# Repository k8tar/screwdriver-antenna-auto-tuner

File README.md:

# Screwdriver Antenna Auto Tuner

An ESP32-based automatic controller for motorized HF screwdriver antennas.

This repository contains the firmware, generated KiCad design files, enclosure
model, sourcing notes, build documentation, renders, and fabrication outputs for
an in-vehicle automatic antenna tuner with:

- ESP32 control logic
- OLED status display
- motor drive with current-based stall detection
- SWR measurement using an onboard directional coupler
- detachable radio and antenna harnesses
- Tarheel-style sensor support via the 4-wire antenna connector

## Current revision highlights

- single-mode auto-tuner firmware with TUNE, PARK, and jog controls
- power-stage revision to the Murata OKI-78SR fixed 3.3 V regulator
- external SWR jack removed from the PCB revision
- updated enclosure previews and board renders
- regenerated Gerber package in `fab/tuner_gerbers.zip`
- printable enclosure assets can be exported directly from OpenSCAD, with 3MF
	files generated for the current base and lid geometry

## Screenshots

Board render:

Assembled enclosure preview:

Service-open enclosure preview:

## Repository layout

- `firmware/` — PlatformIO firmware, simulation wiring, and firmware spec
- `hardware/` — assembly guide, BOM, sourcing, routing notes, enclosure model
- `hardware/kicad/` — generated KiCad schematic, PCB, netlist, DSN, footprints
- `renders/` — board and enclosure images plus schematic and PCB PDFs
- `fab/` — generated Gerbers and fabrication ZIP package
- `scripts/` — source-of-truth generators for schematic, PCB, BOM, and fab outputs

## Quick start

1. Read the hardware requirements and build notes in `hardware/ASSEMBLY.md`.
2. Review the firmware contract in `firmware/FIRMWARE_SPEC.md`.
3. Build firmware from `firmware/` with PlatformIO.
4. If you are fabricating the PCB, use `fab/tuner_gerbers.zip`.
5. If you are printing the enclosure, use the generated 3MF files in
	`hardware/enclosure/` or export fresh parts from `hardware/enclosure/enclosure.scad`.

## First-time builder checklist

1. Read `hardware/ASSEMBLY.md` start to finish before soldering anything.
2. Confirm you are building the **Murata OKI-78SR** power-stage revision, not the older adjustable U1 variant.
3. Order parts from `hardware/BOM.csv` and review substitutions in `hardware/SOURCING.md`.
4. Verify your enclosure connector choices against `hardware/RADIO_CONNECTOR.md` and `hardware/enclosure/README.md`.
5. Print or export the enclosure parts you want before final panel-harness lengths are cut.
6. Build and test the firmware in `firmware/` before final in-vehicle installation.
7. Power the assembled board from a current-limited bench supply first.
8. Program the ESP32 DevKit over USB and verify the OLED, buttons, PARK, and jog behavior before connecting the antenna.
9. Run `PARK` once after wiring a Tarheel-style sensor harness so the controller establishes home.

## Prerequisites

- Python 3 for the generator scripts
- PlatformIO for firmware builds
- KiCad CLI available through the configured Flatpak commands for schematic/PCB regeneration
- OpenSCAD for enclosure previews and print-file export

## Build and generation

Firmware build:

```bash
cd firmware
pio run
```

Firmware upload:

```bash
cd firmware
pio run -t upload
pio device monitor
```

Hardware regeneration from the repo root:

```bash
python3 scripts/gen_footprints.py
python3 scripts/gen_schematic.py
flatpak run --command=kicad-cli org.kicad.KiCad sch export netlist -o hardware/kicad/tuner.net hardware/kicad/tuner.kicad_sch
flatpak run --command=python3 org.kicad.KiCad scripts/gen_pcb.py
flatpak run --command=python3 org.kicad.KiCad scripts/export_dsn.py
python3 scripts/gen_bom.py
python3 scripts/gen_gerbers.py
```

Enclosure print export:

```bash
cd hardware/enclosure
openscad -D 'part="base"' -o base.stl enclosure.scad
openscad -D 'part="lid"' -o lid.stl enclosure.scad
openscad -D 'part="both"' -o enclosure_full.stl enclosure.scad
openscad -D 'part="base"' -o base.3mf enclosure.scad
openscad -D 'part="lid"' -o lid.3mf enclosure.scad
openscad -D 'part="both"' -o enclosure_full.3mf enclosure.scad
```

## Primary documentation

- `firmware/FIRMWARE_SPEC.md`
- `firmware/src/README.md`
- `hardware/ASSEMBLY.md`
- `hardware/SOURCING.md`
- `hardware/RADIO_CONNECTOR.md`
- `hardware/enclosure/README.md`

## Fabrication outputs

- PCB fabrication ZIP: `fab/tuner_gerbers.zip`
- Individual Gerbers/drill files: `fab/gerbers/`
- Enclosure print files: `hardware/enclosure/base.stl`, `hardware/enclosure/lid.stl`, `hardware/enclosure/enclosure_full.stl`, `hardware/enclosure/base.3mf`, `hardware/enclosure/lid.3mf`, `hardware/enclosure/enclosure_full.3mf`
- Board and enclosure previews: `renders/`

## Programming the ESP32

This design uses an ESP32 DevKit module as `U2`, so the easiest programming path
is through the DevKit's normal USB port.

Typical workflow:

1. Assemble the board and fit the ESP32 DevKit at `U2`.
2. Power the board from a current-limited 12 V bench supply for first bring-up.
3. Connect the ESP32 DevKit USB port to your computer.
4. From the `firmware/` directory, run:

```bash
pio run -t upload
pio device monitor
```

If you ever need direct serial flashing instead of the DevKit USB connector, use
the debug UART header `J8` with a 3.3 V USB-to-UART adapter.

Recommended `J8` signals:

- pin 1 = GND
- pin 2 = 3V3
- pin 3 = TX from ESP32
- pin 4 = RX to ESP32

For most builds, you do **not** need to power the ESP32 through `J8`; just share
ground and use the DevKit USB interface unless you have a special recovery case.

## Notes

- The generated KiCad files in `hardware/kicad/` are derived artifacts; the
	Python scripts in `scripts/` are the source of truth.
- For vehicle use, internal board wiring should be direct-soldered and strain
	relieved rather than using loose jumper leads.
- The pre-generated STL and 3MF files are convenience outputs for the current
	enclosure geometry; regenerate them from `hardware/enclosure/enclosure.scad` if
	you change any enclosure parameters. `enclosure_full.3mf` and
	`enclosure_full.stl` contain the base and lid together as one combined export.

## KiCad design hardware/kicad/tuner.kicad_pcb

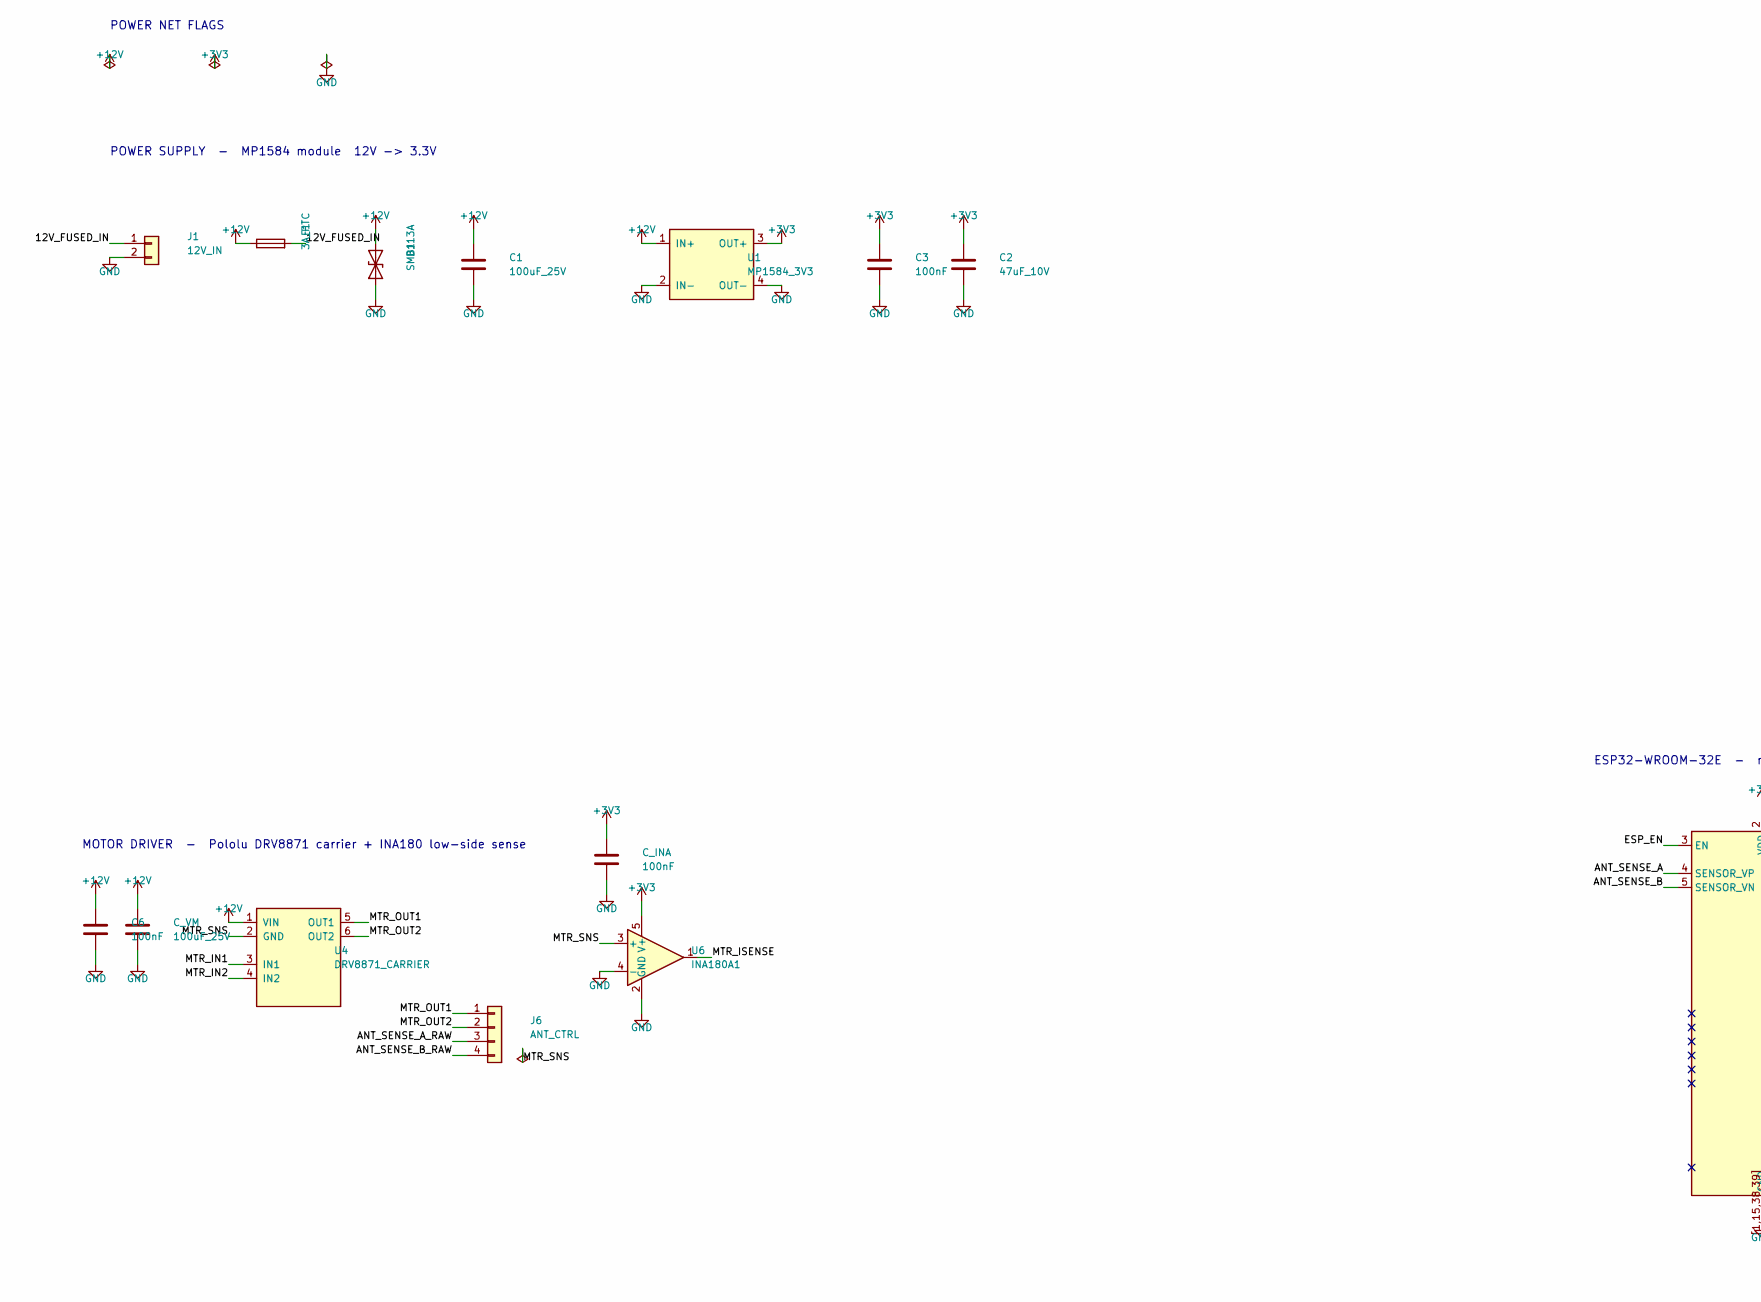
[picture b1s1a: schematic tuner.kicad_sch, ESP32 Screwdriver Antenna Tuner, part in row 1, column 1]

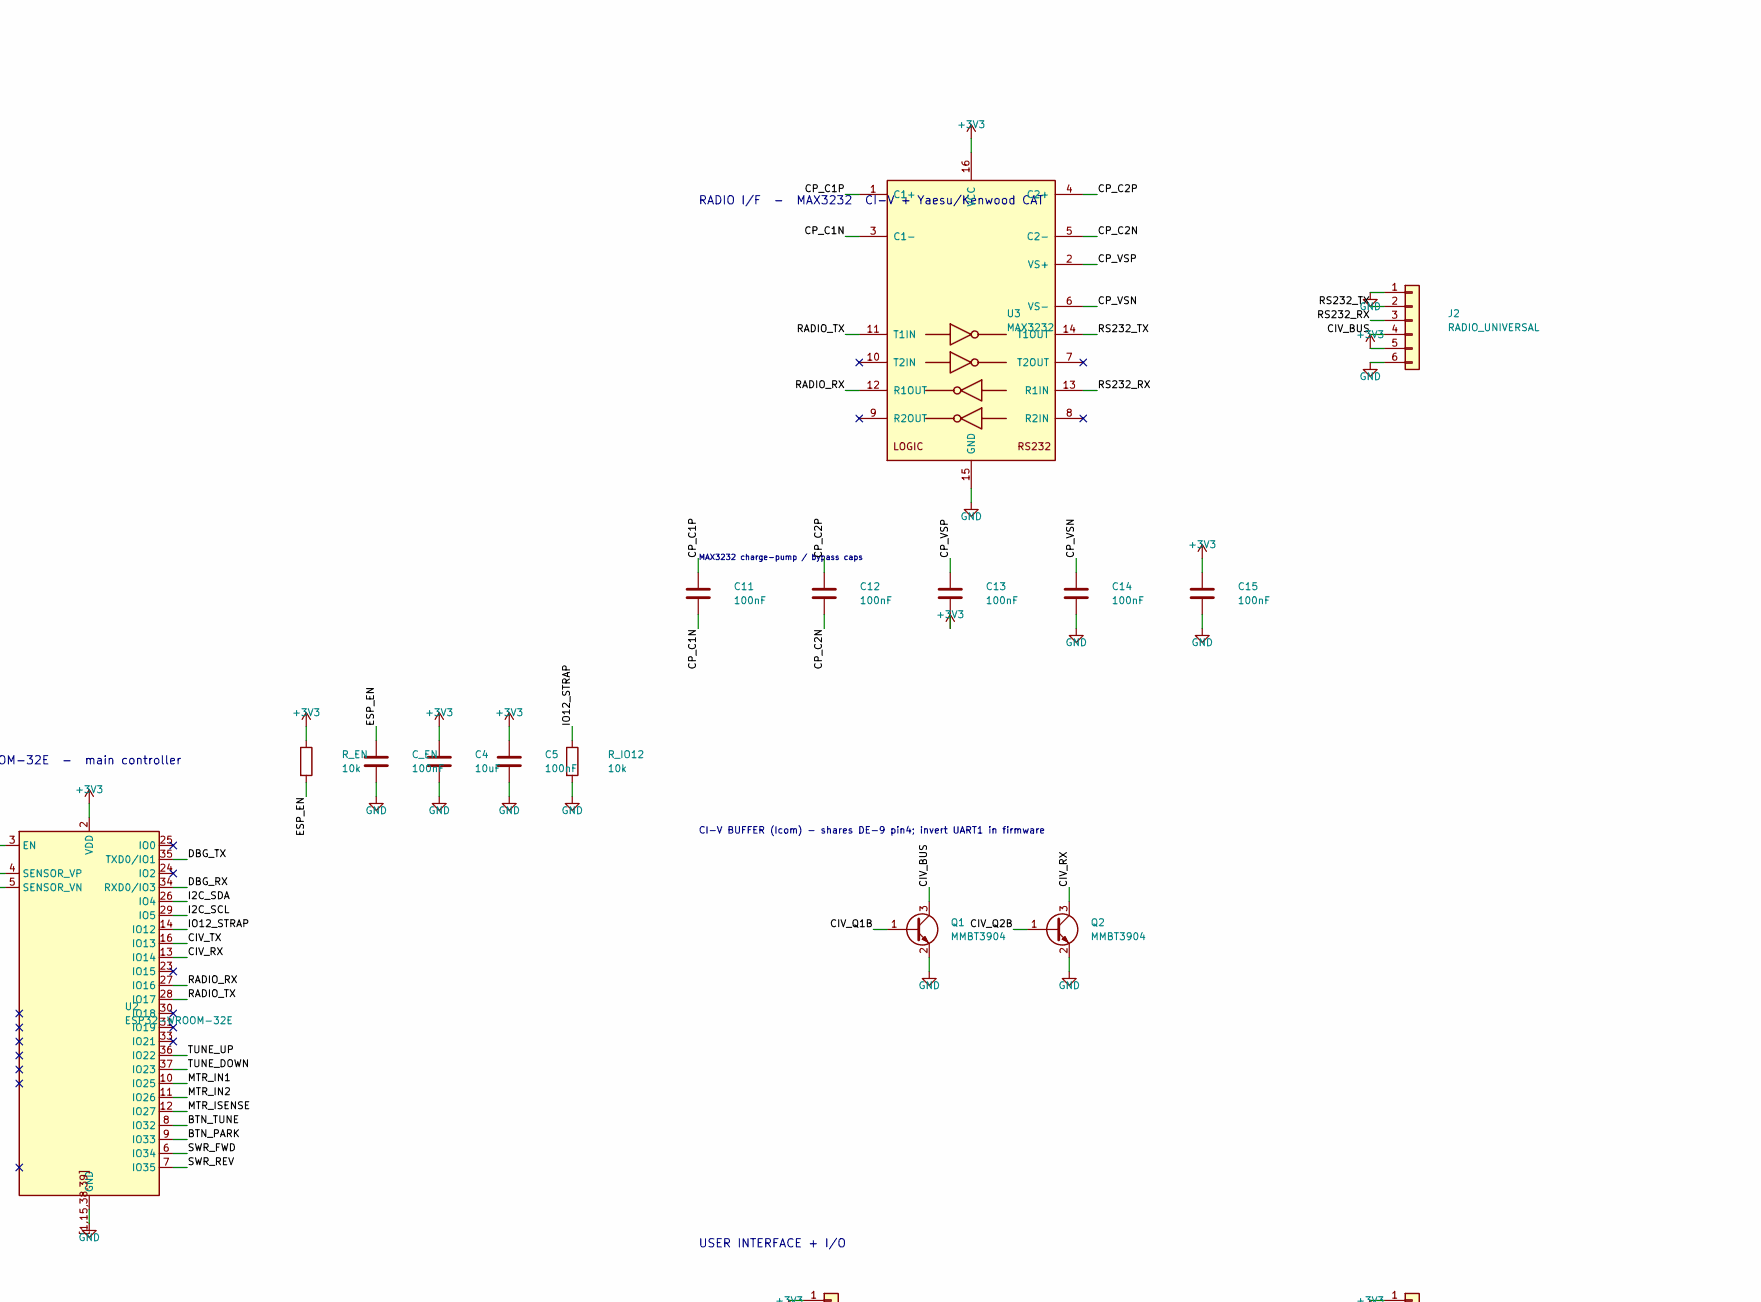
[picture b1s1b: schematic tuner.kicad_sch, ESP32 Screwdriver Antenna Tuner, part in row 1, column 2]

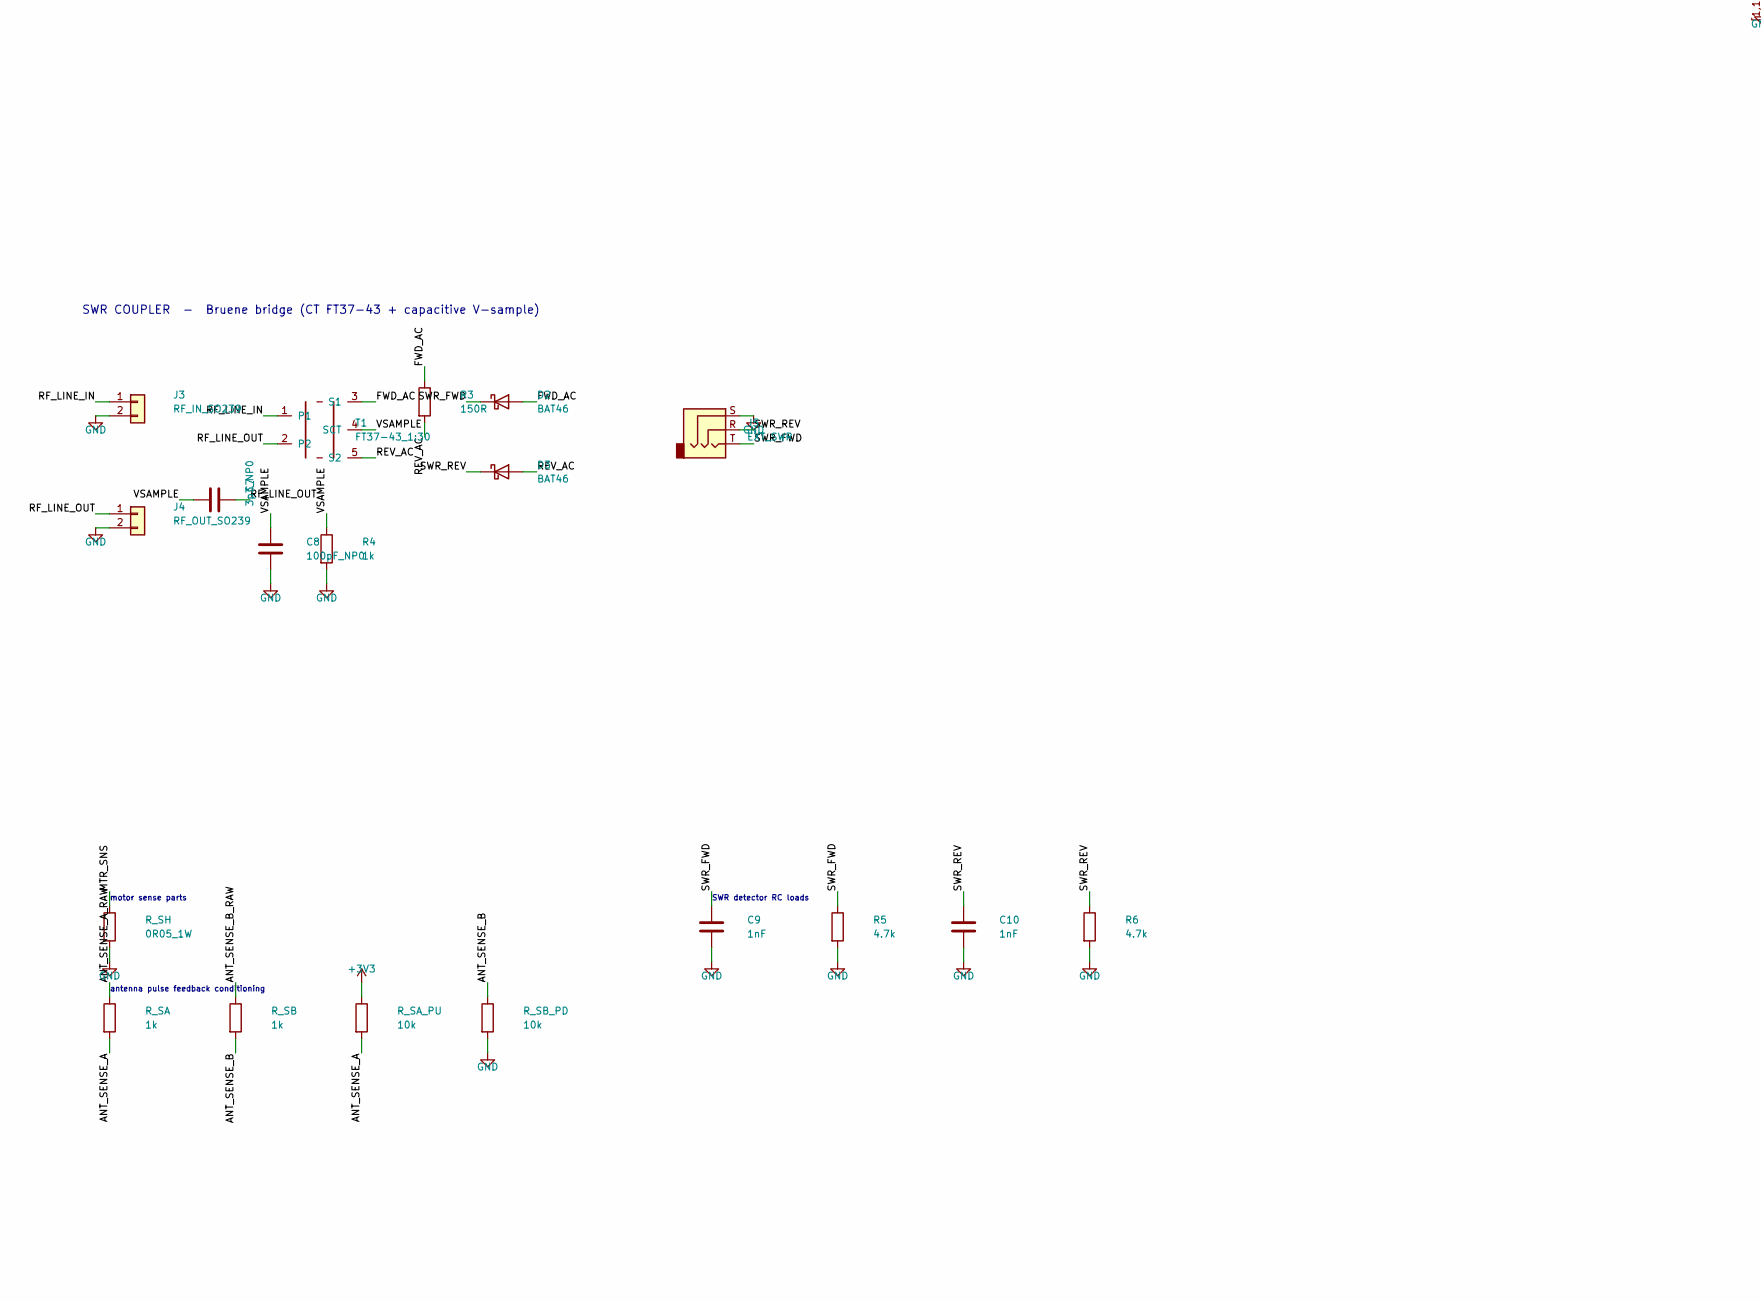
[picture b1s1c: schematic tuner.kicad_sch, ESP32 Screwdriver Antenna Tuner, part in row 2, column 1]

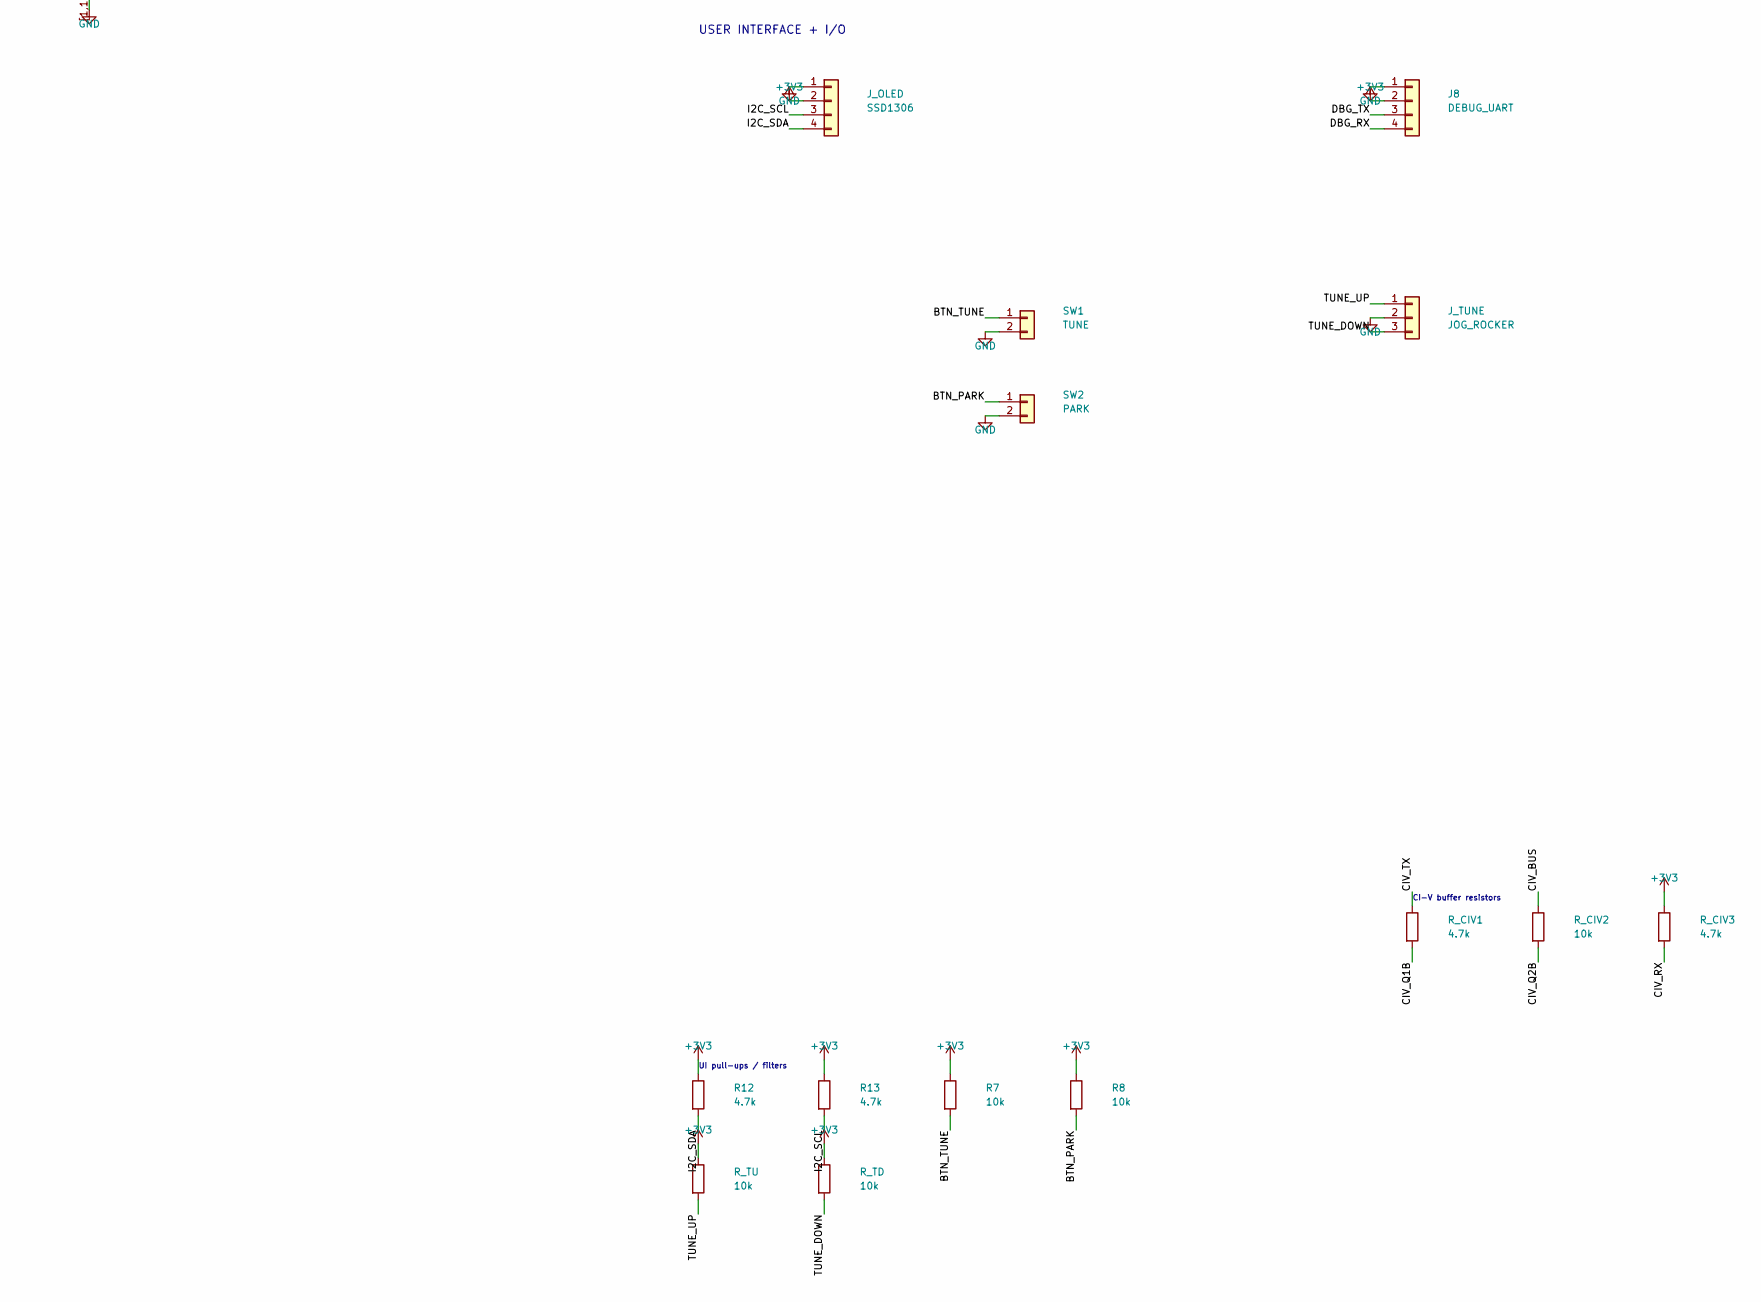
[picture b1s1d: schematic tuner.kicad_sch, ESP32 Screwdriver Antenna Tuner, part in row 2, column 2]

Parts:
C1: 100uF_25V; CP_Elec_6.3x5.4
C2: 47uF_10V; CP_Elec_5x5.4
C3, C5, C6, C11, C12, C13, C14, C15: 100nF; C_0805_2012Metric
C4: 10uF; C_0805_2012Metric
C7: 3p3_NP0; C_0805_2012Metric
C8: 100pF_NP0; C_0805_2012Metric
C9, C10: 1nF; C_0805_2012Metric
C_EN: 100nF; C_0805_2012Metric
C_INA: 100nF; C_0805_2012Metric
C_VM: 100uF_25V; CP_Elec_6.3x5.4
D1: SMBJ13A; D_SMB; MPN SMBJ13A-E3/52
D2, D3: BAT46; D_SOD-323; MPN BAT46WJ
F1: 3A_PTC; Fuse_1812_4532Metric; MPN 1812L300PR
J1: 12V_IN; PinHeader_1x02_P2.54mm_Vertical
J2: RADIO_UNIVERSAL; PinHeader_1x06_P2.54mm_Vertical
J3: RF_IN_SO239; PinHeader_1x02_P2.54mm_Vertical
J4: RF_OUT_SO239; PinHeader_1x02_P2.54mm_Vertical
J5: EXT_SWR; Jack_3.5mm_CUI_SJ1-3533NG_Horizontal
J6: ANT_CTRL; PinHeader_1x04_P2.54mm_Vertical
J8: DEBUG_UART; PinHeader_1x04_P2.54mm_Vertical
J_OLED: SSD1306; PinHeader_1x04_P2.54mm_Vertical
J_TUNE: JOG_ROCKER; PinHeader_1x03_P2.54mm_Vertical
Q1, Q2: MMBT3904; SOT-23
R3: 150R; R_0805_2012Metric
R4: 1k; R_0805_2012Metric
R5, R6, R12, R13: 4.7k; R_0805_2012Metric
R7, R8: 10k; R_0805_2012Metric
R_CIV1, R_CIV3: 4.7k; R_0805_2012Metric
R_CIV2: 10k; R_0805_2012Metric
R_EN: 10k; R_0805_2012Metric
R_IO12: 10k; R_0805_2012Metric
R_SA: 1k; R_0805_2012Metric
R_SA_PU: 10k; R_0805_2012Metric
R_SB: 1k; R_0805_2012Metric
R_SB_PD: 10k; R_0805_2012Metric
R_SH: 0R05_1W; R_2512_6332Metric
R_TD: 10k; R_0805_2012Metric
R_TU: 10k; R_0805_2012Metric
SW1: TUNE; PinHeader_1x02_P2.54mm_Vertical
SW2: PARK; PinHeader_1x02_P2.54mm_Vertical
T1: FT37-43_1:30; CT_FT37_43_Toroid
U1: MP1584_3V3; BUCK_MP1584
U2: ESP32-WROOM-32E; ESP32_DevKit_30; MPN ESP32 DevKit V1 30-pin (DOIT/NodeMCU-32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
U3: MAX3232; SOIC-16_3.9x9.9mm_P1.27mm; MPN MAX3232ESE+
U4: DRV8871_CARRIER
U6: INA180A1; SOT-23-5; MPN INA180A1IDBVR

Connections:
+3V3: C2.1, C3.1, C4.1, C5.1, C13.2, C15.1, C_INA.1, J2.5, J8.2, J_OLED.2, R7.1, R8.1, R12.1, R13.1, R_CIV3.1, R_EN.1, R_SA_PU.1, R_TD.1, R_TU.1, U1.3 (OUT+), U2.2 (VDD), U3.16 (VCC), U6.5 (V+)
+12V: C1.1, C6.1, C_VM.1, D1.2 (A2), F1.1, U1.1 (IN+), U4.1 (VIN)
/12V_FUSED_IN: F1.2, J1.1
/ANT_SENSE_A: R_SA.2, R_SA_PU.2, U2.4 (SENSOR_VP)
/ANT_SENSE_A_RAW: J6.3, R_SA.1
/ANT_SENSE_B: R_SB.2, R_SB_PD.1, U2.5 (SENSOR_VN)
/ANT_SENSE_B_RAW: J6.4, R_SB.1
/BTN_PARK: R8.2, SW2.1, U2.9 (IO33)
/BTN_TUNE: R7.2, SW1.1, U2.8 (IO32)
/CIV_BUS: J2.4, Q1.3 (C), R_CIV2.1
/CIV_Q1B: Q1.1 (B), R_CIV1.2
/CIV_Q2B: Q2.1 (B), R_CIV2.2
/CIV_RX: Q2.3 (C), R_CIV3.2, U2.13 (IO14)
/CIV_TX: R_CIV1.1, U2.16 (IO13)
/CP_C1N: C11.2, U3.3 (C1-)
/CP_C1P: C11.1, U3.1 (C1+)
/CP_C2N: C12.2, U3.5 (C2-)
/CP_C2P: C12.1, U3.4 (C2+)
/CP_VSN: C14.1, U3.6 (VS-)
/CP_VSP: C13.1, U3.2 (VS+)
/DBG_RX: J8.4, U2.34 (RXD0/IO3)
/DBG_TX: J8.3, U2.35 (TXD0/IO1)
/ESP_EN: C_EN.1, R_EN.2, U2.3 (EN)
/FWD_AC: D2.2 (A), R3.1, T1.3 (S1)
/I2C_SCL: J_OLED.3, R13.2, U2.29 (IO5)
/I2C_SDA: J_OLED.4, R12.2, U2.26 (IO4)
/IO12_STRAP: R_IO12.1, U2.14 (IO12)
/MTR_IN1: U2.10 (IO25), U4.3 (IN1)
/MTR_IN2: U2.11 (IO26), U4.4 (IN2)
/MTR_ISENSE: U2.12 (IO27), U6.1
/MTR_OUT1: J6.1, U4.5 (OUT1)
/MTR_OUT2: J6.2, U4.6 (OUT2)
/MTR_SNS: R_SH.1, U4.2 (GND), U6.3 (+)
/RADIO_RX: U2.27 (IO16), U3.12 (R1OUT)
/RADIO_TX: U2.28 (IO17), U3.11 (T1IN)
/REV_AC: D3.2 (A), R3.2, T1.5 (S2)
/RF_LINE_IN: J3.1, T1.1
/RF_LINE_OUT: C7.2, J4.1, T1.2
/RS232_RX: J2.3, U3.13 (R1IN)
/RS232_TX: J2.2, U3.14 (T1OUT)
/SWR_FWD: C9.1, D2.1 (K), J5.T, R5.1, U2.6 (IO34)
/SWR_REV: C10.1, D3.1 (K), J5.R, R6.1, U2.7 (IO35)
/TUNE_DOWN: J_TUNE.3, R_TD.2, U2.37 (IO23)
/TUNE_UP: J_TUNE.1, R_TU.2, U2.36 (IO22)
/VSAMPLE: C7.1, C8.1, R4.1, T1.4 (SCT)
GND: C1.2, C2.2, C3.2, C4.2, C5.2, C6.2, C8.2, C9.2, C10.2, C14.2, C15.2, C_EN.2, C_INA.2, C_VM.2, D1.1 (A1), J1.2, J2.1, J2.6, J3.2, J4.2, J5.S, J8.1, J_OLED.1, J_TUNE.2, Q1.2 (E), Q2.2 (E), R4.2, R5.2, R6.2, R_IO12.2, R_SB_PD.2, R_SH.2, SW1.2, SW2.2, U1.2 (IN-), U1.4 (OUT-), U2.1, U2.15, U2.[1,15,38,39] (GND), U3.15 (GND), U6.2 (GND), U6.4 (-)

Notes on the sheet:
POWER NET FLAGS
POWER SUPPLY - MP1584 module 12V -> 3.3V
ESP32-WROOM-32E - main controller
MOTOR DRIVER - Pololu DRV8871 carrier + INA180 low-side sense
motor sense parts
antenna pulse feedback conditioning
SWR COUPLER - Bruene bridge (CT FT37-43 + capacitive V-sample)
SWR detector RC loads
RADIO I/F - MAX3232 CI-V + Yaesu/Kenwood CAT
MAX3232 charge-pump / bypass caps
CI-V BUFFER (Icom) - shares DE-9 pin4; invert UART1 in firmware
CI-V buffer resistors
USER INTERFACE + I/O
UI pull-ups / filters

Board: 4 copper layers, 61 parts (0 on the bottom side), 46 nets, no tracks yet.

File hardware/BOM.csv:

Ref,Qty,Value,Footprint,MPN,Designators
C1,2,100uF_25V,Capacitor_SMD:CP_Elec_6.3x5.4,EEE-FK1E101P,"C1,C_VM"
C2,1,47uF_10V,Capacitor_SMD:CP_Elec_5x5.4,EEE-FK1C470P,"C2"
C3,10,100nF,Capacitor_SMD:C_0805_2012Metric,CL21B104KBCNNNC,"C3,C5,C6,C11,C12,C13,C14,C15,C_EN,C_INA"
C4,1,10uF,Capacitor_SMD:C_0805_2012Metric,GRM21BR61C106KE15L,"C4"
C7,1,3p3_NP0,Capacitor_SMD:C_0805_2012Metric,08055A3R3CAT2A,"C7"
C8,1,100pF_NP0,Capacitor_SMD:C_0805_2012Metric,CL21C101JBANNNC,"C8"
C9,2,1nF,Capacitor_SMD:C_0805_2012Metric,CL21B102KBANNNC,"C9,C10"
D1,1,SMBJ13A,Diode_SMD:D_SMB,SMBJ13A-E3/52,"D1"
D2,2,BAT46,Diode_SMD:D_SOD-323,BAT46WS,"D2,D3"
F1,1,3A_PTC,Fuse:Fuse_1812_4532Metric,1812L300/24SLER,"F1"
J1,3,12V_IN / RF_IN_SO239 / RF_OUT_SO239,Connector_PinHeader_2.54mm:PinHeader_1x02_P2.54mm_Vertical,61300211121,"J1,J3,J4"
J2,1,RADIO_UNIVERSAL,Connector_PinHeader_2.54mm:PinHeader_1x06_P2.54mm_Vertical,61300611121,"J2"
J5,1,EXT_SWR,Connector_Audio:Jack_3.5mm_CUI_SJ1-3533NG_Horizontal,SJ1-3533NG,"J5"
J6,3,ANT_CTRL / DEBUG_UART / SSD1306,Connector_PinHeader_2.54mm:PinHeader_1x04_P2.54mm_Vertical,61300411121,"J6,J8,J_OLED"
J_TUNE,1,JOG_ROCKER,Connector_PinHeader_2.54mm:PinHeader_1x03_P2.54mm_Vertical,61300311121,"J_TUNE"
Q1,2,MMBT3904,Package_TO_SOT_SMD:SOT-23,MMBT3904LT1G,"Q1,Q2"
R3,1,150R,Resistor_SMD:R_0805_2012Metric,RC0805FR-07150RL,"R3"
R4,3,1k,Resistor_SMD:R_0805_2012Metric,RC0805FR-071KL,"R4,R_SA,R_SB"
R5,6,4.7k,Resistor_SMD:R_0805_2012Metric,RC0805FR-074K7L,"R5,R6,R12,R13,R_CIV1,R_CIV3"
R7,9,10k,Resistor_SMD:R_0805_2012Metric,RC0805FR-0710KL,"R7,R8,R_CIV2,R_EN,R_IO12,R_SA_PU,R_SB_PD,R_TD,R_TU"
R_SH,1,0R05_1W,Resistor_SMD:R_2512_6332Metric,WSL2512R0500FEA,"R_SH"
SW1,2,PARK / TUNE,Connector_PinHeader_2.54mm:PinHeader_1x02_P2.54mm_Vertical,PTS645VL58-2LFS,"SW1,SW2"
T1,1,FT37-43_1:30,Tuner:CT_FT37_43_Toroid,5943000201,"T1"
U1,1,MP1584_3V3,Tuner:BUCK_MP1584,MP1584EN-module,"U1"
U2,1,ESP32-WROOM-32E,Tuner:ESP32_DevKit_30,ESP32 DevKit V1 30-pin (DOIT/NodeMCU-32S),"U2"
U3,1,MAX3232,Package_SO:SOIC-16_3.9x9.9mm_P1.27mm,MAX3232ESE+,"U3"
U4,1,DRV8871_CARRIER,Tuner:DRV8871_CARRIER,POLOLU-2990,"U4"
U6,1,INA180A1,Package_TO_SOT_SMD:SOT-23-5,INA180A1IDBVR,"U6"
P_RF_MINIUHF,2,RF_BULKHEAD_MINI_UHF_PANEL_F,Panel_Mount:Offboard,Amphenol RF 172147,"PANEL_RF_IN,PANEL_RF_OUT"
P_RF_ADAPT_UHF,2,ADAPTER_MINIUHF_M_TO_UHF_F,Connector_RF:Offboard,Amphenol RF 242132,"RF_IN_PANEL_ADAPTER,RF_OUT_PANEL_ADAPTER"
W_RF_RG316,1,RG316_50OHM_COAX_1M,Wire:Offboard,RG-316 coax cable 1 m,"RF_PIGTAIL_IN,RF_PIGTAIL_OUT"
P_RADIO_GX16_PANEL,1,GX16_PANEL_FEMALE_6PIN,Panel_Mount:Offboard,GX16-6 panel bulkhead female,"RADIO_PANEL"
P_RADIO_GX16_PLUG,3,GX16_CABLE_MALE_6PIN,Panel_Mount:Offboard,GX16-6 cable male plug,"RADIO_CABLE_ICOM,RADIO_CABLE_YAESU,RADIO_CABLE_KENWOOD"
P_MOTOR_GX16_PANEL,1,GX16_PANEL_FEMALE_4PIN,Panel_Mount:Offboard,GX16-4 panel bulkhead female,"ANTENNA_PANEL"
P_MOTOR_GX16_PLUG,2,GX16_CABLE_MALE_4PIN,Panel_Mount:Offboard,GX16-4 cable male plug,"ANTENNA_CABLE_PRIMARY,ANTENNA_CABLE_SPARE"
P_MOTOR_TARHEEL_KIT,1,TARHEEL_MOLEX_4PIN_KIT,Connector_Offboard,Tarheel Molex Kit (4-pin inline pair + pins + heat shrink),"ANTENNA_CABLE_TARHEEL"
W_RADIO_CTRL,1,SHIELDED_MULTICORE_24-26AWG_3M,Wire:Offboard,Shielded multicore cable 24-26 AWG 3 m,"RADIO_CABLE_ICOM,RADIO_CABLE_YAESU,RADIO_CABLE_KENWOOD"
W_MOTOR_4C,1,MOTOR_CABLE_4C_18-22AWG_2M,Wire:Offboard,4-conductor stranded cable 18-22 AWG 2 m,"ANTENNA_CABLE_PRIMARY"
W_MOTOR_4C_TARHEEL,1,MOTOR_CABLE_4C_18-22AWG_1M,Wire:Offboard,4-conductor stranded cable 18-22 AWG 1 m,"ANTENNA_CABLE_TARHEEL"
P_CIV_3P5MM,1,ICOM_CIV_3P5MM_PLUG,Connector_Audio:Offboard,3.5 mm mono plug solder type,"RADIO_CABLE_ICOM"
P_CAT_DB9F,1,KENWOOD_CAT_DB9F,Connector_DSub:Offboard,DE-9 female solder-cup connector + hood,"RADIO_CABLE_KENWOOD"
P_CAT_MINIDIN8,1,YAESU_CAT_MINIDIN8,Connector_DIN:Offboard,Mini-DIN-8 male solder plug,"RADIO_CABLE_YAESU"

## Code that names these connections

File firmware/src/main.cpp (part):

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#include <driver/uart.h>

namespace Pins {
constexpr int I2C_SDA = 4;
constexpr int I2C_SCL = 5;

constexpr int RADIO_RX = 16;
constexpr int RADIO_TX = 17;
constexpr int CIV_TX = 13;
constexpr int CIV_RX = 14;

constexpr int MTR_IN1 = 25;
constexpr int MTR_IN2 = 26;
constexpr int MTR_ISENSE = 27;

constexpr int SWR_FWD = 34;
constexpr int SWR_REV = 35;
constexpr int ANT_SENSE_A = 36;
constexpr int ANT_SENSE_B = 39;

constexpr int BTN_TUNE = 32;
constexpr int BTN_PARK = 33;
constexpr int TUNE_UP = 22;
constexpr int TUNE_DOWN = 23;
}  // namespace Pins

namespace Cfg {
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class MotorController {
 public:
  void begin() {
    pinMode(Pins::MTR_IN1, OUTPUT);
    pinMode(Pins::MTR_IN2, OUTPUT);
    ledcSetup(kChan1, Cfg::PWM_FREQ_HZ, Cfg::PWM_BITS);
    ledcSetup(kChan2, Cfg::PWM_FREQ_HZ, Cfg::PWM_BITS);
    ledcAttachPin(Pins::MTR_IN1, kChan1);
    ledcAttachPin(Pins::MTR_IN2, kChan2);
    stopCoast();
  }

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    dir_ = MotorDir::BRAKE;
    targetDuty_ = 0;
    currentDuty_ = 0;
    digitalWrite(Pins::MTR_IN1, HIGH);
    digitalWrite(Pins::MTR_IN2, HIGH);
  }

  void stopCoast() {
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    currentDuty_ = 0;
    ledcWrite(kChan1, 0);
    ledcWrite(kChan2, 0);
    digitalWrite(Pins::MTR_IN1, LOW);
    digitalWrite(Pins::MTR_IN2, LOW);
  }

 private:
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    if (dir_ == MotorDir::BRAKE) {
      ledcWrite(kChan1, 0);
      ledcWrite(kChan2, 0);
      digitalWrite(Pins::MTR_IN1, HIGH);
      digitalWrite(Pins::MTR_IN2, HIGH);
      return;
    }
    if (dir_ == MotorDir::COAST) {
      ledcWrite(kChan1, 0);
      ledcWrite(kChan2, 0);
      digitalWrite(Pins::MTR_IN1, LOW);
      digitalWrite(Pins::MTR_IN2, LOW);
      return;
    }

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class AntennaFeedback {
 public:
  void begin() {
    pinMode(Pins::ANT_SENSE_A, INPUT);
    pinMode(Pins::ANT_SENSE_B, INPUT);
    aStable_ = digitalRead(Pins::ANT_SENSE_A);
    bStable_ = digitalRead(Pins::ANT_SENSE_B);
    lastRawA_ = aStable_;
    lastRawB_ = bStable_;
  }

  void update(uint32_t nowMs, MotorDir dir) {
    bool rawA = digitalRead(Pins::ANT_SENSE_A);
    bool rawB = digitalRead(Pins::ANT_SENSE_B);

    if (rawA != lastRawA_) {
      lastRawA_ = rawA;
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class RadioManager {
 public:
  void begin() {
    Serial1.begin(19200, SERIAL_8N1, Pins::CIV_RX, Pins::CIV_TX);
    uart_set_line_inverse(UART_NUM_1, UART_SIGNAL_RXD_INV | UART_SIGNAL_TXD_INV);
    Serial2.begin(9600, SERIAL_8N1, Pins::RADIO_RX, Pins::RADIO_TX);
  }

  void applyConfig(const RadioConfig& cfg) {
    cfg_ = cfg;
    if (cfg_.proto == RadioProto::CIV && cfg_.baud > 0) {
      Serial1.begin(cfg_.baud, SERIAL_8N1, Pins::CIV_RX, Pins::CIV_TX);
      uart_set_line_inverse(UART_NUM_1, UART_SIGNAL_RXD_INV | UART_SIGNAL_TXD_INV);
    }
    if ((cfg_.proto == RadioProto::CAT_ASCII || cfg_.proto == RadioProto::YAESU_OLD_BIN) && cfg_.baud > 0) {
      Serial2.begin(cfg_.baud, SERIAL_8N1, Pins::RADIO_RX, Pins::RADIO_TX);
    }
  }

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
    const uint32_t civBauds[] = {19200, 9600, 4800};
    for (uint32_t b : civBauds) {
      Serial1.begin(b, SERIAL_8N1, Pins::CIV_RX, Pins::CIV_TX);
      uart_set_line_inverse(UART_NUM_1, UART_SIGNAL_RXD_INV | UART_SIGNAL_TXD_INV);
      if (probeCiv(out)) {
        out.detected = true;
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
    const uint32_t catBauds[] = {9600, 4800, 38400, 57600, 115200};
    for (uint32_t b : catBauds) {
      Serial2.begin(b, SERIAL_8N1, Pins::RADIO_RX, Pins::RADIO_TX);
      if (probeKenwood()) {
        out.detected = true;
        out.brand = RadioBrand::KENWOOD;
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}

bool anyControlPressedRaw() {
  return !digitalRead(Pins::BTN_TUNE) || !digitalRead(Pins::BTN_PARK) ||
         !digitalRead(Pins::TUNE_UP) || !digitalRead(Pins::TUNE_DOWN);
}

void waitForPostAcknowledge() {
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}

void updateMeasurements() {
  int fwd = readAveragedAdc(Pins::SWR_FWD, Cfg::ADC_SAMPLES);
  int rev = readAveragedAdc(Pins::SWR_REV, Cfg::ADC_SAMPLES);
  int isense = readAveragedAdc(Pins::MTR_ISENSE, 8);

  g_meas.vfwd = max(0.0f, adcToVolts(fwd) - g_cal.fwdOffsetV);
  g_meas.vrev = max(0.0f, adcToVolts(rev) - g_cal.revOffsetV);
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
  pinMode(12, INPUT);

  g_btnTune.begin(Pins::BTN_TUNE, true, true);
  g_btnPark.begin(Pins::BTN_PARK, true, true);
  g_btnUp.begin(Pins::TUNE_UP, true, true);
  g_btnDown.begin(Pins::TUNE_DOWN, true, true);

  analogReadResolution(12);
  analogSetPinAttenuation(Pins::SWR_FWD, ADC_11db);
  analogSetPinAttenuation(Pins::SWR_REV, ADC_11db);
  analogSetPinAttenuation(Pins::MTR_ISENSE, ADC_11db);

  Wire.begin(Pins::I2C_SDA, Pins::I2C_SCL);
  g_oled.begin();
  g_oled.clearBuffer();
  g_oled.setFont(u8g2_font_6x12_tr);
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
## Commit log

2026-06-15 Initial tuner firmware and hardware baseline
2026-06-15 Revise power stage and refresh hardware artifacts
2026-06-15 Add release summary and changelog
2026-06-15 Clean up redundant generated artifacts
2026-06-15 Add print assets and builder checklist
2026-06-15 Fix lid pass-through placement and refresh print assets
2026-06-15 Switch jog to through-button holes and add enclosure engravings
2026-06-15 Finalize assembly notes and enclosure artifact refresh
